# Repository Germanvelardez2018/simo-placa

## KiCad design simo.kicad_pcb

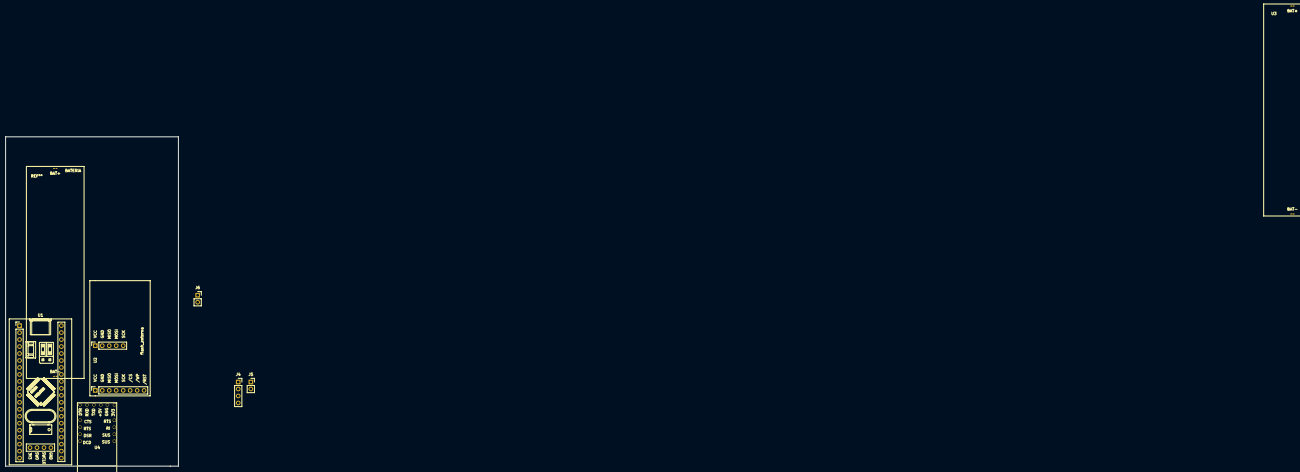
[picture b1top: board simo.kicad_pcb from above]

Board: 2 copper layers, 63.0 x 120.0 mm, 7 parts (0 on the bottom side), 14 nets, no tracks yet.

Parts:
J4: Conn_01x04_Female; PinSocket_1x04_P2.54mm_Vertical
J5, J6: Conn_01x02_Female; PinSocket_1x02_P2.54mm_Vertical
U1: YAAJ_BlackPill_Part_Like_SWD_Breakout; YAAJ_BluePill_SWD_1
U2: flash_externa; conector_flash_ext
U3: bateria
U4: USB_DEBUG; debug_usb

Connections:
unnamed: J4.1, U1.38
unnamed: J4.2, U1.37
unnamed: J4.3, U1.36
unnamed: J4.4, U1.35
unnamed: J5.1, U1.34
unnamed: J5.2, U1.33
unnamed: U1.11, U2.5
unnamed: U1.12, U2.3
unnamed: U1.13, U2.4
unnamed: U1.16, U2.1
unnamed: U1.17, U1.18, U2.2
unnamed: U1.19, U2.6
unnamed: U1.25, U4.3
unnamed: U1.26, U4.2

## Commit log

2022-05-10 placa de conexion
2022-05-11 se termino template y huella del modulo 4g sim7000g
2022-05-11 update, eliminando archivos innecesarios
2022-05-12 se agregaron huellas de : memoria flash ext, debug_usb y conversor_dc_dc
2022-05-12 se agrego huella de mpu6050
